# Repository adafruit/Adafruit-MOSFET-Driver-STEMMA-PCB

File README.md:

## Adafruit Adafruit MOSFET Driver STEMMA PCB

<a href="http://www.adafruit.com/products/5648"><br/>
Click here to purchase one from the Adafruit shop</a>

PCB files for the Adafruit Adafruit MOSFET Driver STEMMA. 

Format is EagleCAD schematic and board layout
* https://www.adafruit.com/product/5648

### Description

Sparky the Blue Smoke Monster shows up whenever the magic smoke is let of of an electronic component. And his very favorite is whenever folks first start with electronics and robotics: wiring up a motor or solenoid or high power LED is a perfect recipe for getting that blue smoke out of an Arduino or Raspberry Pi. Why? Because these high-current devices can't be connected directly to a GPIO pin on a microcontroller! They need to have a transistor / MOSFET driver, plus a kickback-protection diode that will absorb the inductive 'kick' caused by turning on-and-off motors and solenoids. Without that driver and diode - your tronix will go poof!

We have tutorials on how to wire up the components to create a transistor driver on a breadboard, but its easy to put the diode in backwards, or pick the wrong kind of transistor. And some folks don't want to have the extra breadboard for just controlling a simple motor fan or solenoid. Which is why we designed the Adafruit STEMMA MOSFET Driver for Motors, Solenoids, and LEDs. 

This board has a simple plug-and-play JST PH (2mm pitch) input connector for solderless use. Provide power (from 3V up to 30V) and signal (3V to 20V logic level). On the output are two-output terminal blocks, with one block connected to power and the other switched to ground when the signal level is high. In between is an AO3406 N-Channel MOSFET rated for  30Vds, 3.6A peak, and 70mΩ RdsOn plus a 1N4007 flyback diode.

You can also get to all the signal and power pins on a 0.1" breakout header if desired, but we expect most folks will like using it as a solderless MOSFET-buddy. Great for driving motors, inductors, high power LEDs, single-color LED strips, or other loads up with to 1.5 Amps continuous draw, 3 Amp peak. Note that the JST PH connector itself is only rated for 2 Amp continuous.

### License

Adafruit invests time and resources providing this open source design, please support Adafruit and open-source hardware by purchasing products from [Adafruit](https://www.adafruit.com)!

Designed by Limor Fried/Ladyada for Adafruit Industries.

Creative Commons Attribution/Share-Alike, all text above must be included in any redistribution. 
See license.txt for additional details.

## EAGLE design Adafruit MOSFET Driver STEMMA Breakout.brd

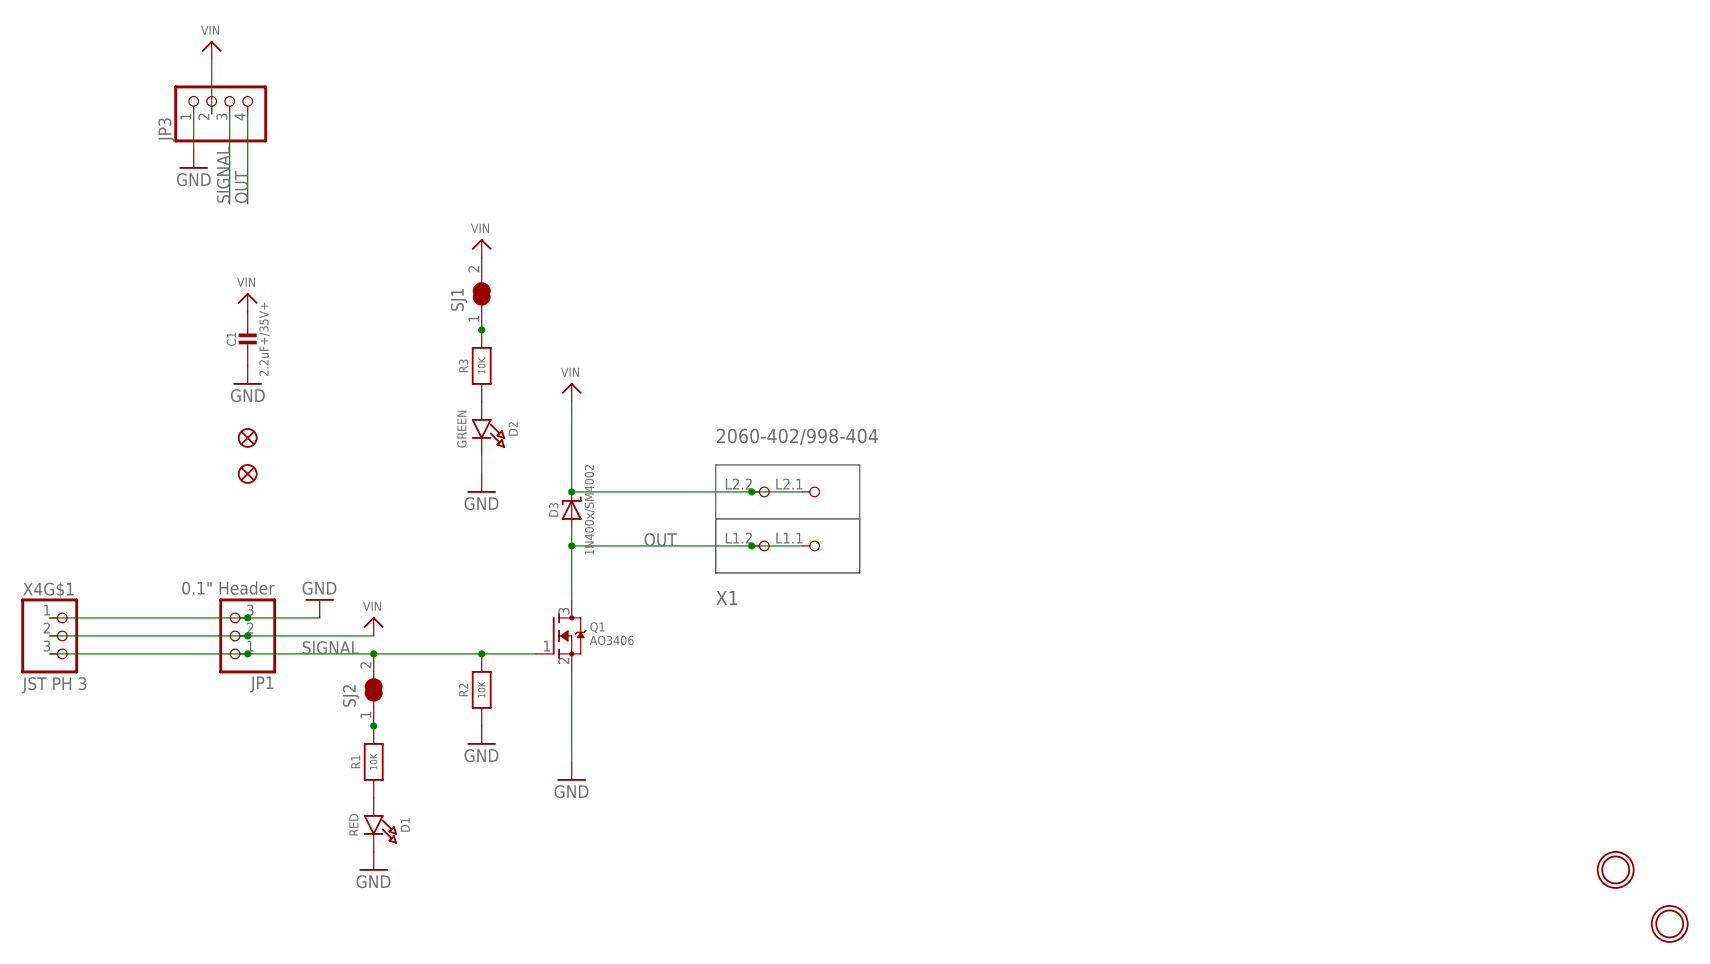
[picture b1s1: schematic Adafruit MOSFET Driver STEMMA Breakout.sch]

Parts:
C1: 2.2uF+/35V+; 0805-NO
D1: RED; CHIPLED_0603_NOOUTLINE
D2: GREEN; CHIPLED_0603_NOOUTLINE
D3: 1N400x/SM4002; SOD-123
FID2, FID3: FIDUCIAL_1MM
JP1: 0.1" Header; 1X03_OVAL
JP3: HEADER-1X4ROUND; 1X04_ROUND
Q1: AO3406; SOT23-WIDE
R1, R2, R3: 10K; 0603-NO
SJ1, SJ2: SOLDERJUMPER_CLOSED; SOLDERJUMPER_CLOSEDWIRE
U$1, U$8: MOUNTINGHOLE2.5; MOUNTINGHOLE_2.5_PLATED
X1: 2060-402/998-404; P-2060-402/998-404
X4: JST PH 3; JSTPH3

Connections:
GND: C1.2, D1.C, D2.C, JP1.3, JP3.1, Q1.2 (S), R2.1, X4.1
unnamed: R3.2, SJ1.1
unnamed: D1.A, R1.1
unnamed: R1.2, SJ2.1
unnamed: D2.A, R3.1
OUT: D3.A, JP3.4, Q1.3 (D), X1.L1.1 (P1.1), X1.L1.2 (P1.2)
SIGNAL: JP1.1, JP3.3, Q1.1 (G), R2.2, SJ2.2, X4.3
VIN: C1.1, D3.C, JP1.2, JP3.2, SJ1.2, X1.L2.1 (P2.1), X1.L2.2 (P2.2), X4.2

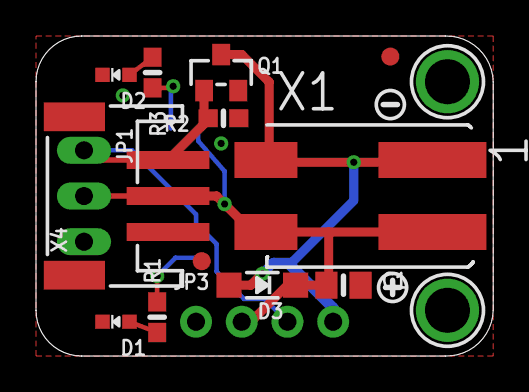
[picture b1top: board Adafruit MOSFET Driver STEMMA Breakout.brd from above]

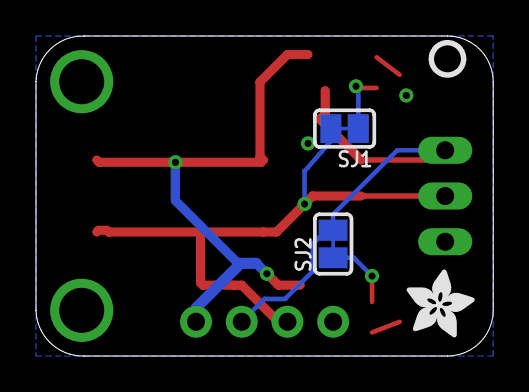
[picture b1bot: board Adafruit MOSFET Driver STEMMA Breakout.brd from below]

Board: 2 copper layers, 25.4 x 17.8 mm, 36 parts (15 on the bottom side), 8 nets.

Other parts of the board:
PLABEL0: PLABEL0
PLABEL1: PLABEL1
PLABEL2: PLABEL2
PLABEL3: PLABEL3
PLABEL4: PLABEL4
PLABEL5: PLABEL5
PLABEL6: PLABEL6
PLABEL7: PLABEL7
PLABEL8: PLABEL8
PLABEL9: PLABEL9
PLABEL10: PLABEL10
PLABEL11: PLABEL11
PLABEL12: PLABEL12
PLABEL13: PLABEL13
U$3: SYMBOL_PLUS
U$5: PCBFEAT-REV-040
U$9: SYMBOL_MINUS
U$12: ADAFRUIT_3.5MM

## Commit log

2022-12-12 adding cookiecutter output
2022-12-12 adding measures

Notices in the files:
parts and their libraries:
microbuilder: This work is placed in the public domain, and may be freely used for commercial and non-commercial work with the following conditions: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
